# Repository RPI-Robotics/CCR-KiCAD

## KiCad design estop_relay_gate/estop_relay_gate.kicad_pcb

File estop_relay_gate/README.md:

# Emergency Stop Relay Gate PCB

A custom board to take in two active low emergency stop signals and shut off relays instantaneously upon the loss of one emergency stop signals. I'm designing it in KiCAD to remove any risk of vehicle vibrations loosening solder connections.

The board mounts with 4 M2 screw holes on the corners. It is powered by 5V from the central power system, and takes in two inputs from the physical and wireless emergency stops. It outputs into two control lines for solid state relays powering 2 ODrive motor controllers.

**Status:** Version 1 Gerber and Drill files created. Ordering very soon (I hope).

## Schematic

**Rough breakdown:**

- Circuit takes two active low signals as input which are fed into an AND logic gate.

- AND gate controls an nMOS MOSFET which powers two Normally Open solid state relays.

- Upon the loss of one emergency stop signal, solid state relays shut off and indicator LED's switch.

## PCB Layout

PCB dimensions are 31mm x 56.5mm.

## ToDo List

- [x] Design PCB layout.

- [ ] Order board and parts.

- [ ] Assemble and test.

## Credits

Original design by James Qiu for RPI Robotics Club, 2026.

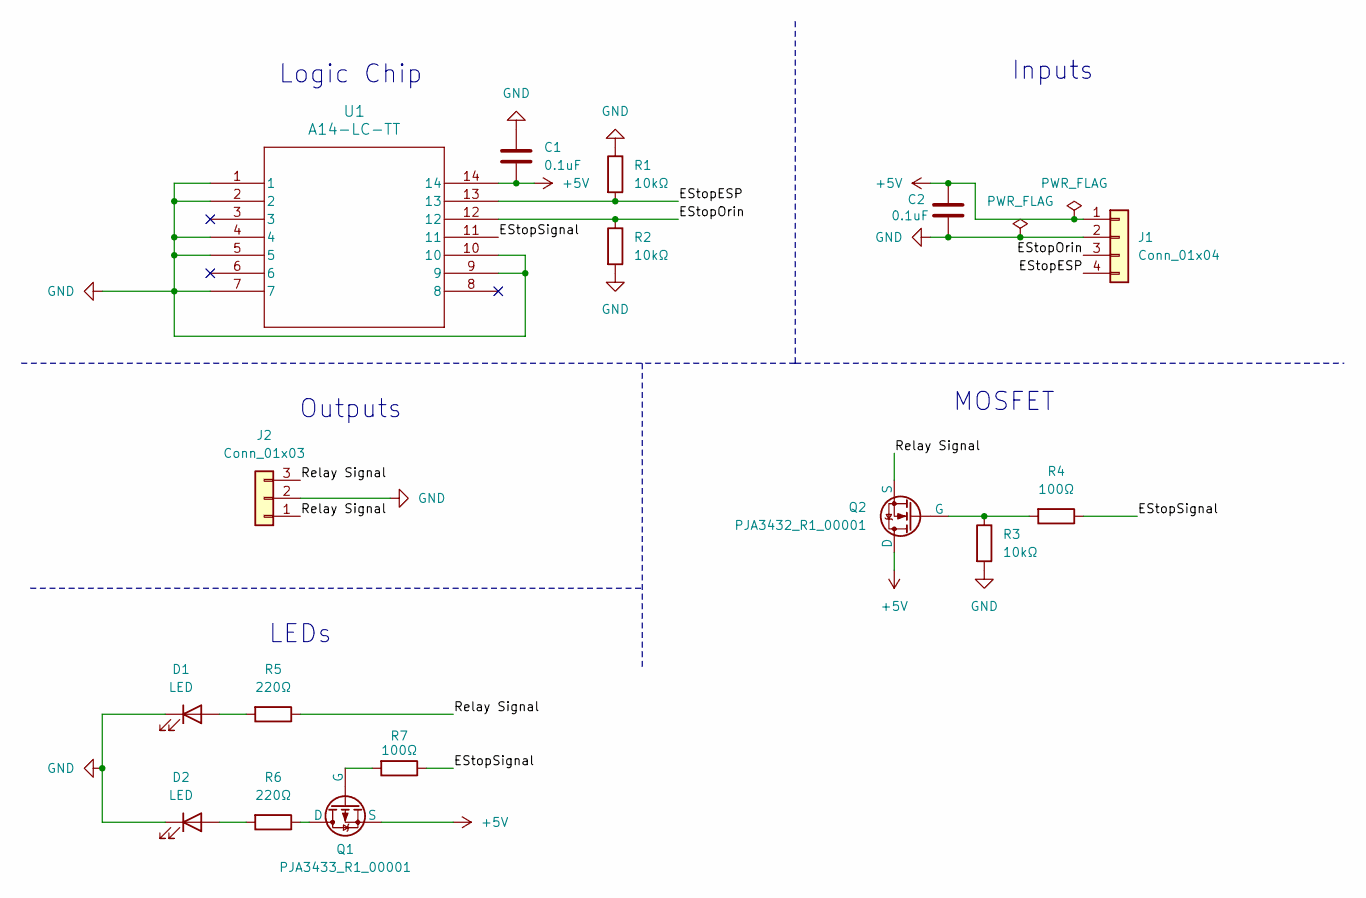
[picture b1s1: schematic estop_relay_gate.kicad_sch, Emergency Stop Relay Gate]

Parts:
C1, C2: 0.1uF; C_0805_2012Metric_Pad1.18x1.45mm_HandSolder
D1, D2: LED; LED_D3.0mm
J1: Conn_01x04; TerminalBlock_Phoenix_MKDS-1,5-4_1x04_P5.00mm_Horizontal
J2: Conn_01x03; TerminalBlock_Phoenix_MKDS-1,5-3_1x03_P5.00mm_Horizontal
Q1: PJA3433_R1_00001
Q2: PJA3432_R1_00001
R1, R2, R3: 10kΩ; R_0805_2012Metric_Pad1.20x1.40mm_HandSolder
R4, R7: 100Ω; R_0805_2012Metric_Pad1.20x1.40mm_HandSolder
R5, R6: 220Ω; R_0805_2012Metric_Pad1.20x1.40mm_HandSolder
U1: A14-LC-TT; A14-LC-TT_ASM

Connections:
+5V: C1.2, C2.1, J1.1, Q1.3 (S), Q2.1 (D), U1.14
/EStopESP: J1.4, R1.2, U1.13
/EStopOrin: J1.3, R2.1, U1.12
/EStopSignal: R4.1, R7.1, U1.11
/Relay Signal: J2.1, J2.3, Q2.3 (S), R5.1
GND: C1.1, C2.2, D1.1 (K), D2.1 (K), J1.2, J2.2, R1.1, R2.2, R3.2, U1.1, U1.2, U1.4, U1.5, U1.7, U1.9, U1.10
unnamed: D1.2 (A), R5.2
unnamed: D2.2 (A), R6.2
unnamed: Q1.1 (D), R6.1
unnamed: Q1.2 (G), R7.2
unnamed: Q2.2 (G), R3.1, R4.2

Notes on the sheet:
Logic Chip
MOSFET
Inputs
Outputs
LEDs

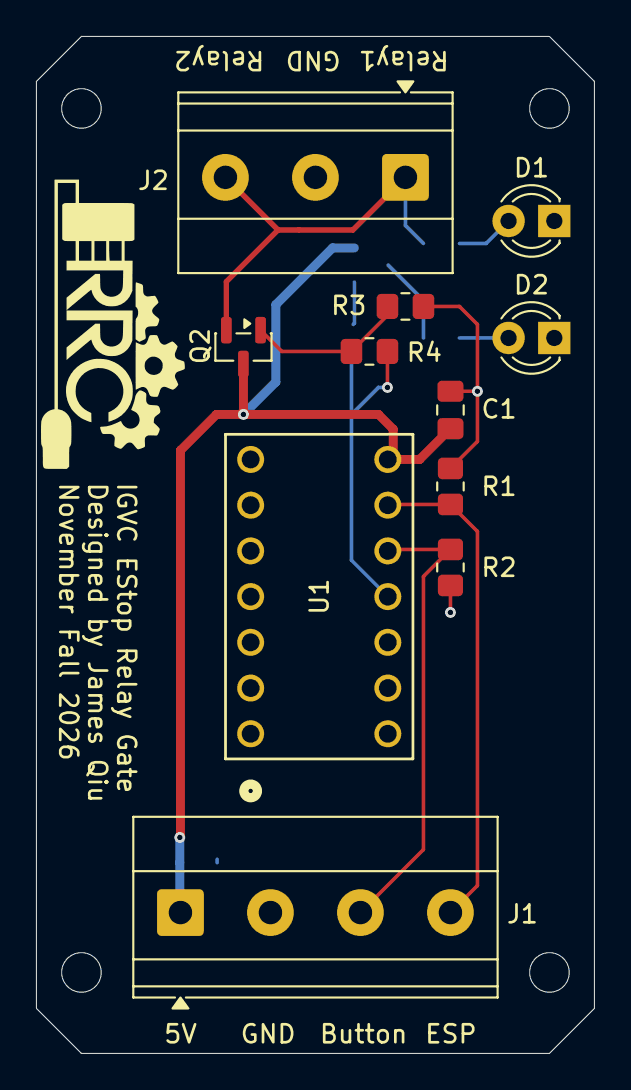
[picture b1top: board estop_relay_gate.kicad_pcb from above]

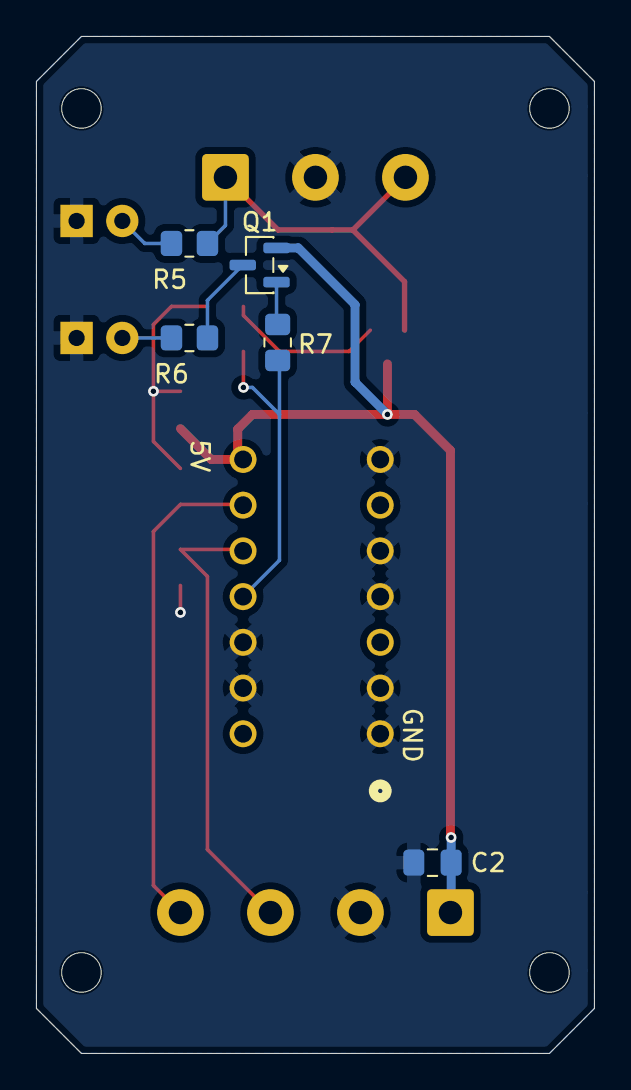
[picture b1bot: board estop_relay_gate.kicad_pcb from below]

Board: 2 copper layers, 31.0 x 56.5 mm, 16 parts (5 on the bottom side), 11 nets.

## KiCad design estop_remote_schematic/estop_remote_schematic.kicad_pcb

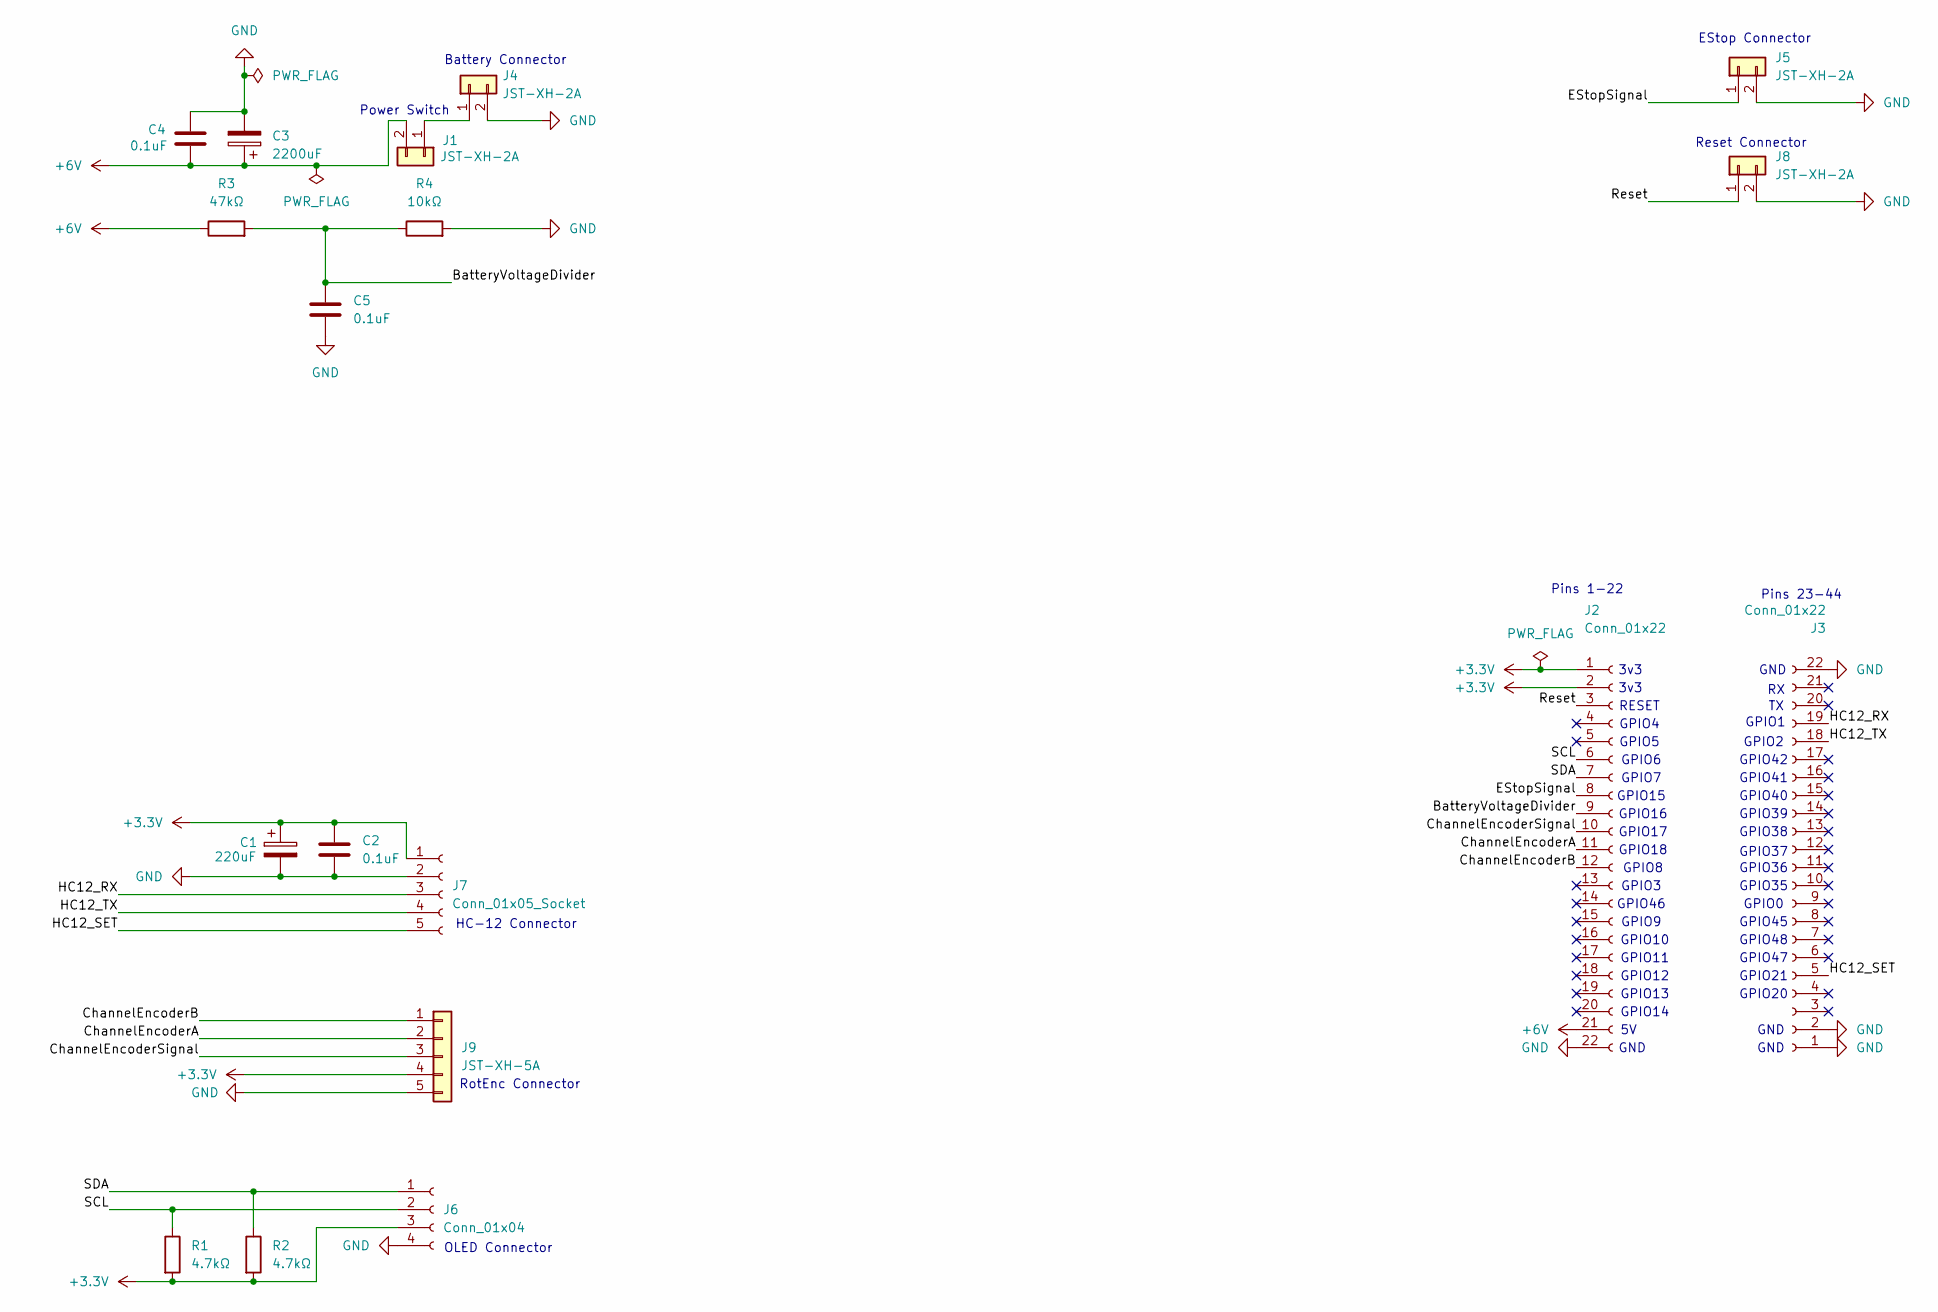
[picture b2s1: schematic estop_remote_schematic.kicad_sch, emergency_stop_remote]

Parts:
C1: 220uF; CP_Radial_D7.5mm_P2.50mm
C2, C4, C5: 0.1uF; C_0603_1608Metric_Pad1.08x0.95mm_HandSolder
C3: 2200uF; CP_Radial_D10.0mm_P5.00mm
J1, J4, J5, J8: JST-XH-2A; JST_XH_B2B-XH-A_1x02_P2.50mm_Vertical
J2, J3: Conn_01x22; PinSocket_1x22_P2.54mm_Vertical
J6: Conn_01x04; JST_XH_B4B-XH-A_1x04_P2.50mm_Vertical
J7: Conn_01x05_Socket
J9: JST-XH-5A; JST_XH_B5B-XH-A_1x05_P2.50mm_Vertical
R1, R2: 4.7kΩ; R_0805_2012Metric_Pad1.20x1.40mm_HandSolder
R3: 47kΩ; R_0805_2012Metric_Pad1.20x1.40mm_HandSolder
R4: 10kΩ; R_0805_2012Metric_Pad1.20x1.40mm_HandSolder

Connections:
+3.3V: C1.1, C2.1, J2.1, J2.2, J6.3, J7.1, J9.4, R1.2, R2.2
+6V: C3.1, C4.2, J1.2, J2.21, R3.1
/BatteryVoltageDivider: C5.1, J2.9, R3.2, R4.1
/ChannelEncoderA: J2.11, J9.2
/ChannelEncoderB: J2.12, J9.1
/ChannelEncoderSignal: J2.10, J9.3
/EStopSignal: J2.8, J5.1
/HC12_RX: J3.19, J7.3
/HC12_SET: J3.5, J7.5
/HC12_TX: J3.18, J7.4
/Reset: J2.3, J8.1
/SCL: J2.6, J6.2, R1.1
/SDA: J2.7, J6.1, R2.1
GND: C1.2, C2.2, C3.2, C4.1, C5.2, J2.22, J3.1, J3.2, J3.22, J4.2, J5.2, J6.4, J7.2, J8.2, J9.5, R4.2
unnamed: J1.1, J4.1

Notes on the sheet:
GPIO1
GPIO10
GPIO14
GPIO45
Battery Connector
GPIO35
GND
Pins 23-44
Reset Connector
GPIO38
GPIO21
GPIO39
GPIO5
GPIO47
GPIO36
GPIO48
GPIO7
GPIO4
HC-12 Connector
GPIO46
GPIO40
GPIO6
GPIO16
GPIO15
RESET
GPIO41
GPIO9
GPIO12
RotEnc Connector
GPIO11
3v3
GPIO8
GPIO0
GPIO18
GPIO17
Pins 1-22
GPIO13
GPIO2
OLED Connector
GPIO42

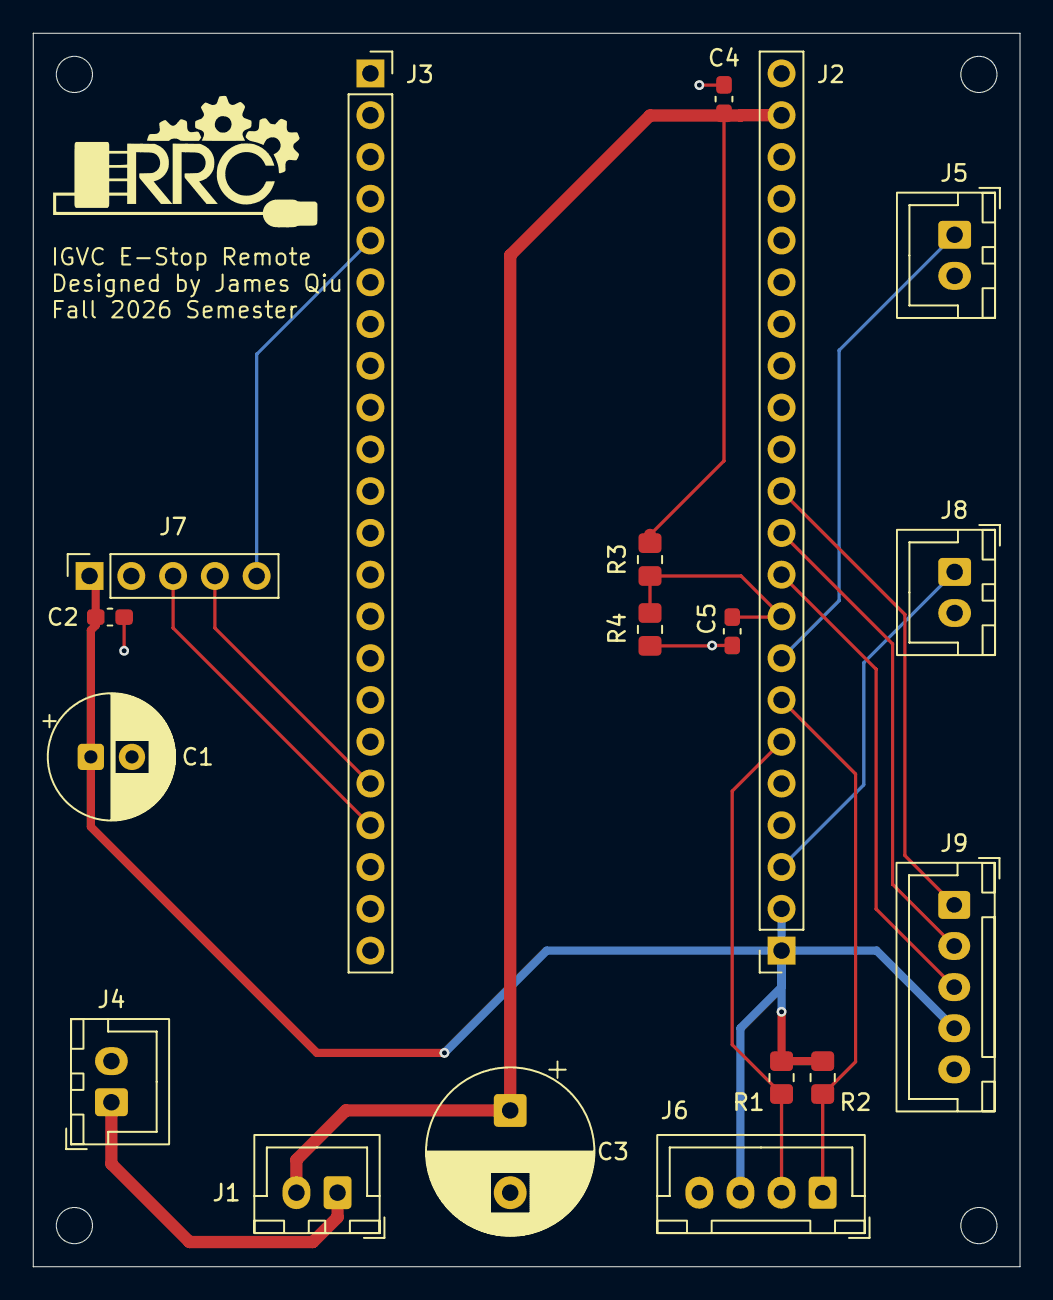
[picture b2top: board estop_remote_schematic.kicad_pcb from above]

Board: 2 copper layers, 60.0 x 75.0 mm, 18 parts (0 on the bottom side), 15 nets.
